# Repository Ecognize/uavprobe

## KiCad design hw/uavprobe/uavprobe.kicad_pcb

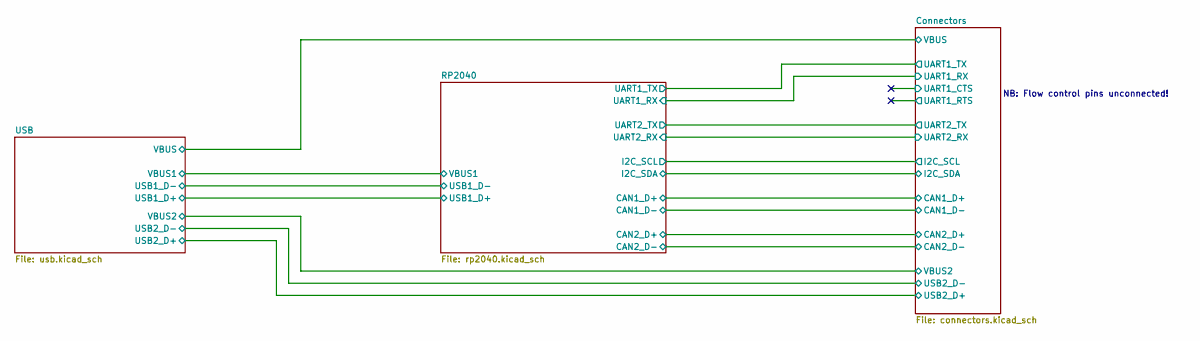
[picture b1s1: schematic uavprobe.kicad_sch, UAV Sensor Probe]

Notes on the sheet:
NB: Flow control pins unconnected!

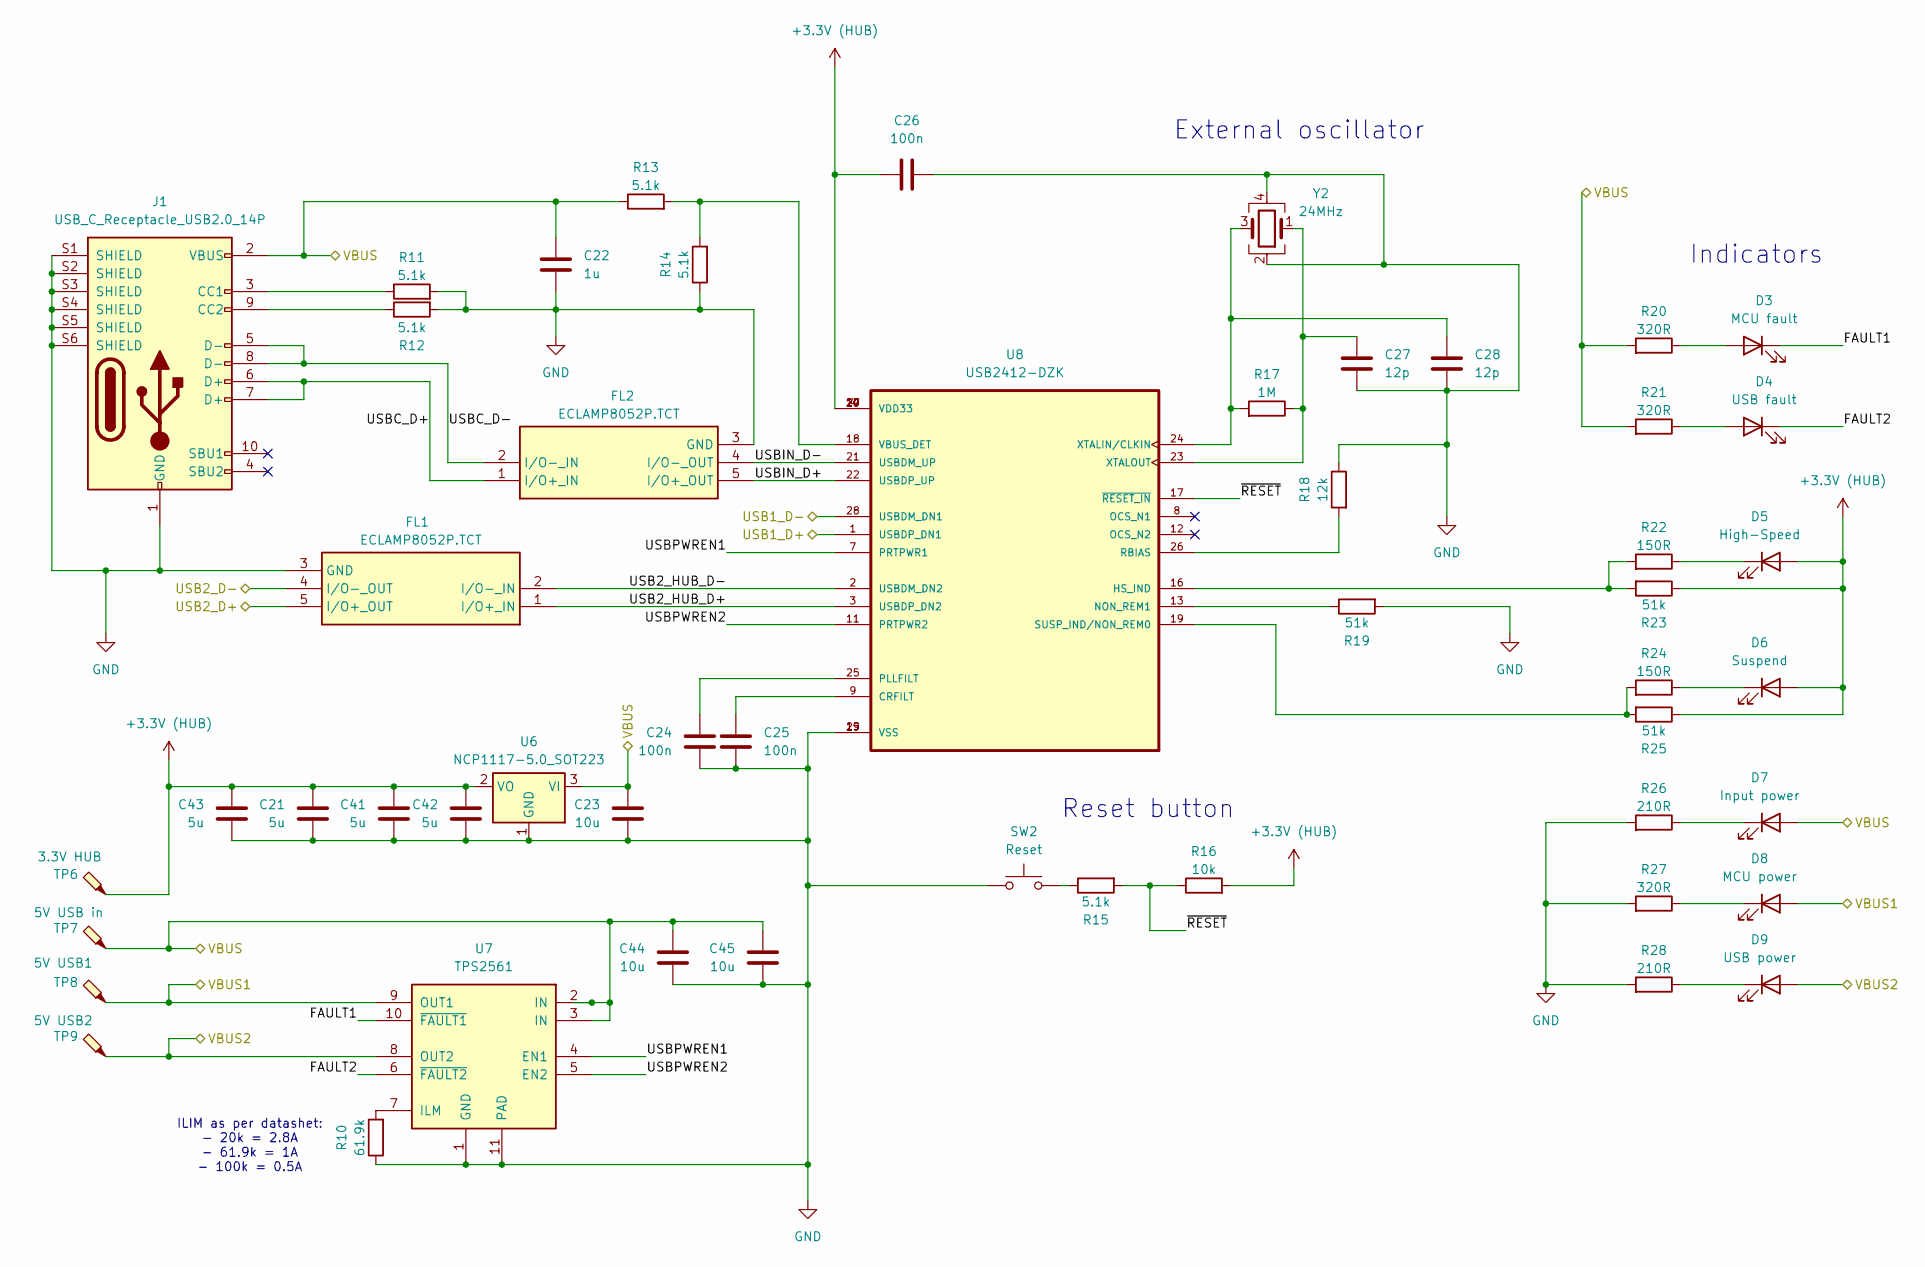
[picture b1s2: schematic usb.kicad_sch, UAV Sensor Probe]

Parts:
C21, C41, C42, C43: 5u; C_0402_1005Metric
C22: 1u; C_0402_1005Metric
C23, C44, C45: 10u; C_0402_1005Metric
C24, C25, C26: 100n; C_0402_1005Metric
C27, C28: 12p; C_0402_1005Metric
D3: MCU fault; LED_0402_1005Metric; MPN QBLP595-R
D4: USB fault; LED_0402_1005Metric; MPN QBLP595-R
D5: High-Speed; LED_0402_1005Metric; MPN QBLP595-O
D6: Suspend; LED_0402_1005Metric; MPN QBLP595-Y
D7: Input power; LED_0402_1005Metric; MPN QBLP595-IG
D8: MCU power; LED_0402_1005Metric; MPN QBLP595-AG
D9: USB power; LED_0402_1005Metric; MPN QBLP595-IB
FL1, FL2: ECLAMP8052P.TCT; ECLAMP8052PTCT; MPN ECLAMP8052P.TCT; Mouser Part Number 947-ECLAMP8052P.TCT
J1: USB_C_Receptacle_USB2.0_14P; JAE_DX07S016JA1R1500; MPN DX07S016JA1R1500
R10: 61.9k; R_0402_1005Metric
R11, R12, R13, R14, R15: 5.1k; R_0402_1005Metric
R16: 10k; R_0402_1005Metric
R17: 1M; R_0402_1005Metric
R18: 12k; R_0402_1005Metric
R19, R23, R25: 51k; R_0402_1005Metric
R20, R21, R27: 320R; R_0402_1005Metric
R22, R24: 150R; R_0402_1005Metric
R26, R28: 210R; R_0402_1005Metric
SW2: Reset; SW_SPST_B3U-1000P; MPN B3U-1000PM
TP6: 3.3V HUB; TestPoint_Pad_D1.5mm
TP7: 5V USB in; TestPoint_Pad_D1.5mm
TP8: 5V USB1; TestPoint_Pad_D1.5mm
TP9: 5V USB2; TestPoint_Pad_D1.5mm
U6: NCP1117-5.0_SOT223; SOT-223-3_TabPin2; MPN NCP1117ST33T3G
U7: TPS2561; VSON-10-1EP_3x3mm_P0.5mm_EP1.65x2.4mm_ThermalVias; MPN TPS2561DRCT
U8: USB2412-DZK; QFN50P500X500X100-29N; MPN USB2412-DZK; DIGI-KEY_PART_NUMBER 638-1114-ND
Y2: 24MHz; Crystal_SMD_Abracon_ABM3B-4Pin_5.0x3.2mm; MPN ABM3B-24.000MHZ-10-1-U-T

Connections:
+3.3V (HUB): C21.1, C26.1, C41.1, C42.1, C43.1, D5.2 (A), D6.2 (A), R16.2, R23.1, R25.1, TP6.1, U6.2 (VO), U8.4 (VDD33), U8.10 (VDD33), U8.14 (VDD33), U8.20 (VDD33), U8.27 (VDD33)
/Connectors/USB2_D+: FL1.5 (I/O+_OUT); also elsewhere on the board
/Connectors/USB2_D-: FL1.4 (I/O-_OUT); also elsewhere on the board
/Connectors/VBUS: C22.1, C23.1, C44.1, C45.1, D7.2 (A), J1.2 (VBUS), J1.11 (VBUS), R13.1, R20.2, R21.2, TP7.1, U6.3 (VI), U7.2 (IN), U7.3 (IN); also elsewhere on the board
/Connectors/VBUS2: D9.2 (A), TP9.1, U7.8 (OUT2); also elsewhere on the board
/RP2040/USB1_D+: U8.1 (USBDP_DN1); also elsewhere on the board
/RP2040/USB1_D-: U8.28 (USBDM_DN1); also elsewhere on the board
/RP2040/VBUS1: D8.2 (A), TP8.1, U7.9 (OUT1); also elsewhere on the board
/USB/FAULT1: D3.1 (K), U7.10 (~FAULT1)
/USB/FAULT2: D4.1 (K), U7.6 (~FAULT2)
/USB/USB2_HUB_D+: FL1.1 (I/O+_IN), U8.3 (USBDP_DN2)
/USB/USB2_HUB_D-: FL1.2 (I/O-_IN), U8.2 (USBDM_DN2)
/USB/USBC_D+: FL2.1 (I/O+_IN), J1.6 (D+), J1.7 (D+)
/USB/USBC_D-: FL2.2 (I/O-_IN), J1.5 (D-), J1.8 (D-)
/USB/USBIN_D+: FL2.5 (I/O+_OUT), U8.22 (USBDP_UP)
/USB/USBIN_D-: FL2.4 (I/O-_OUT), U8.21 (USBDM_UP)
/USB/USBPWREN1: U7.4 (EN1), U8.7 (PRTPWR1)
/USB/USBPWREN2: U7.5 (EN2), U8.11 (PRTPWR2)
/USB/~RESET: R15.2, R16.1, U8.17 (~RESET_IN)
GND: C21.2, C22.2, C23.2, C24.2, C25.2, C26.2, C27.2, C28.2, C41.2, C42.2, C43.2, C44.2, C45.2, FL1.3 (GND), FL2.3 (GND), J1.1 (GND), J1.12 (GND), J1.S1 (SHIELD), J1.S2 (SHIELD), J1.S3 (SHIELD), J1.S4 (SHIELD), J1.S5 (SHIELD), J1.S6 (SHIELD), R10.1, R11.2, R12.2, R14.1, R18.1, R19.2, R26.2, R27.2, R28.2, SW2.1, U6.1 (GND), U7.1 (GND), U7.11 (PAD), U8.15 (VSS), U8.29 (VSS), Y2.2, Y2.4; also elsewhere on the board
unnamed: D3.2 (A), R20.1
unnamed: D4.2 (A), R21.1
unnamed: D5.1 (K), R22.1
unnamed: D6.1 (K), R24.1
unnamed: D7.1 (K), R26.1
unnamed: D8.1 (K), R27.1
unnamed: D9.1 (K), R28.1
unnamed: J1.3 (CC1), R11.1
unnamed: J1.9 (CC2), R12.1
unnamed: R15.1, SW2.2
unnamed: R10.2, U7.7 (ILM)
unnamed: C25.1, U8.9 (CRFILT)
unnamed: R22.2, R23.2, U8.16 (HS_IND)
unnamed: R19.1, U8.13 (NON_REM1)
unnamed: C24.1, U8.25 (PLLFILT)
unnamed: R18.2, U8.26 (RBIAS)
unnamed: R24.2, R25.2, U8.19 (SUSP_IND/NON_REM0)
unnamed: R13.2, R14.2, U8.18 (VBUS_DET)
unnamed: C28.1, R17.2, U8.24 (XTALIN/CLKIN), Y2.3
unnamed: C27.1, R17.1, U8.23 (XTALOUT), Y2.1

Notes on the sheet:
Indicators
ILIM as per datashet: - 20k = 2.8A - 61.9k = 1A - 100k = 0.5A
Reset button
External oscillator

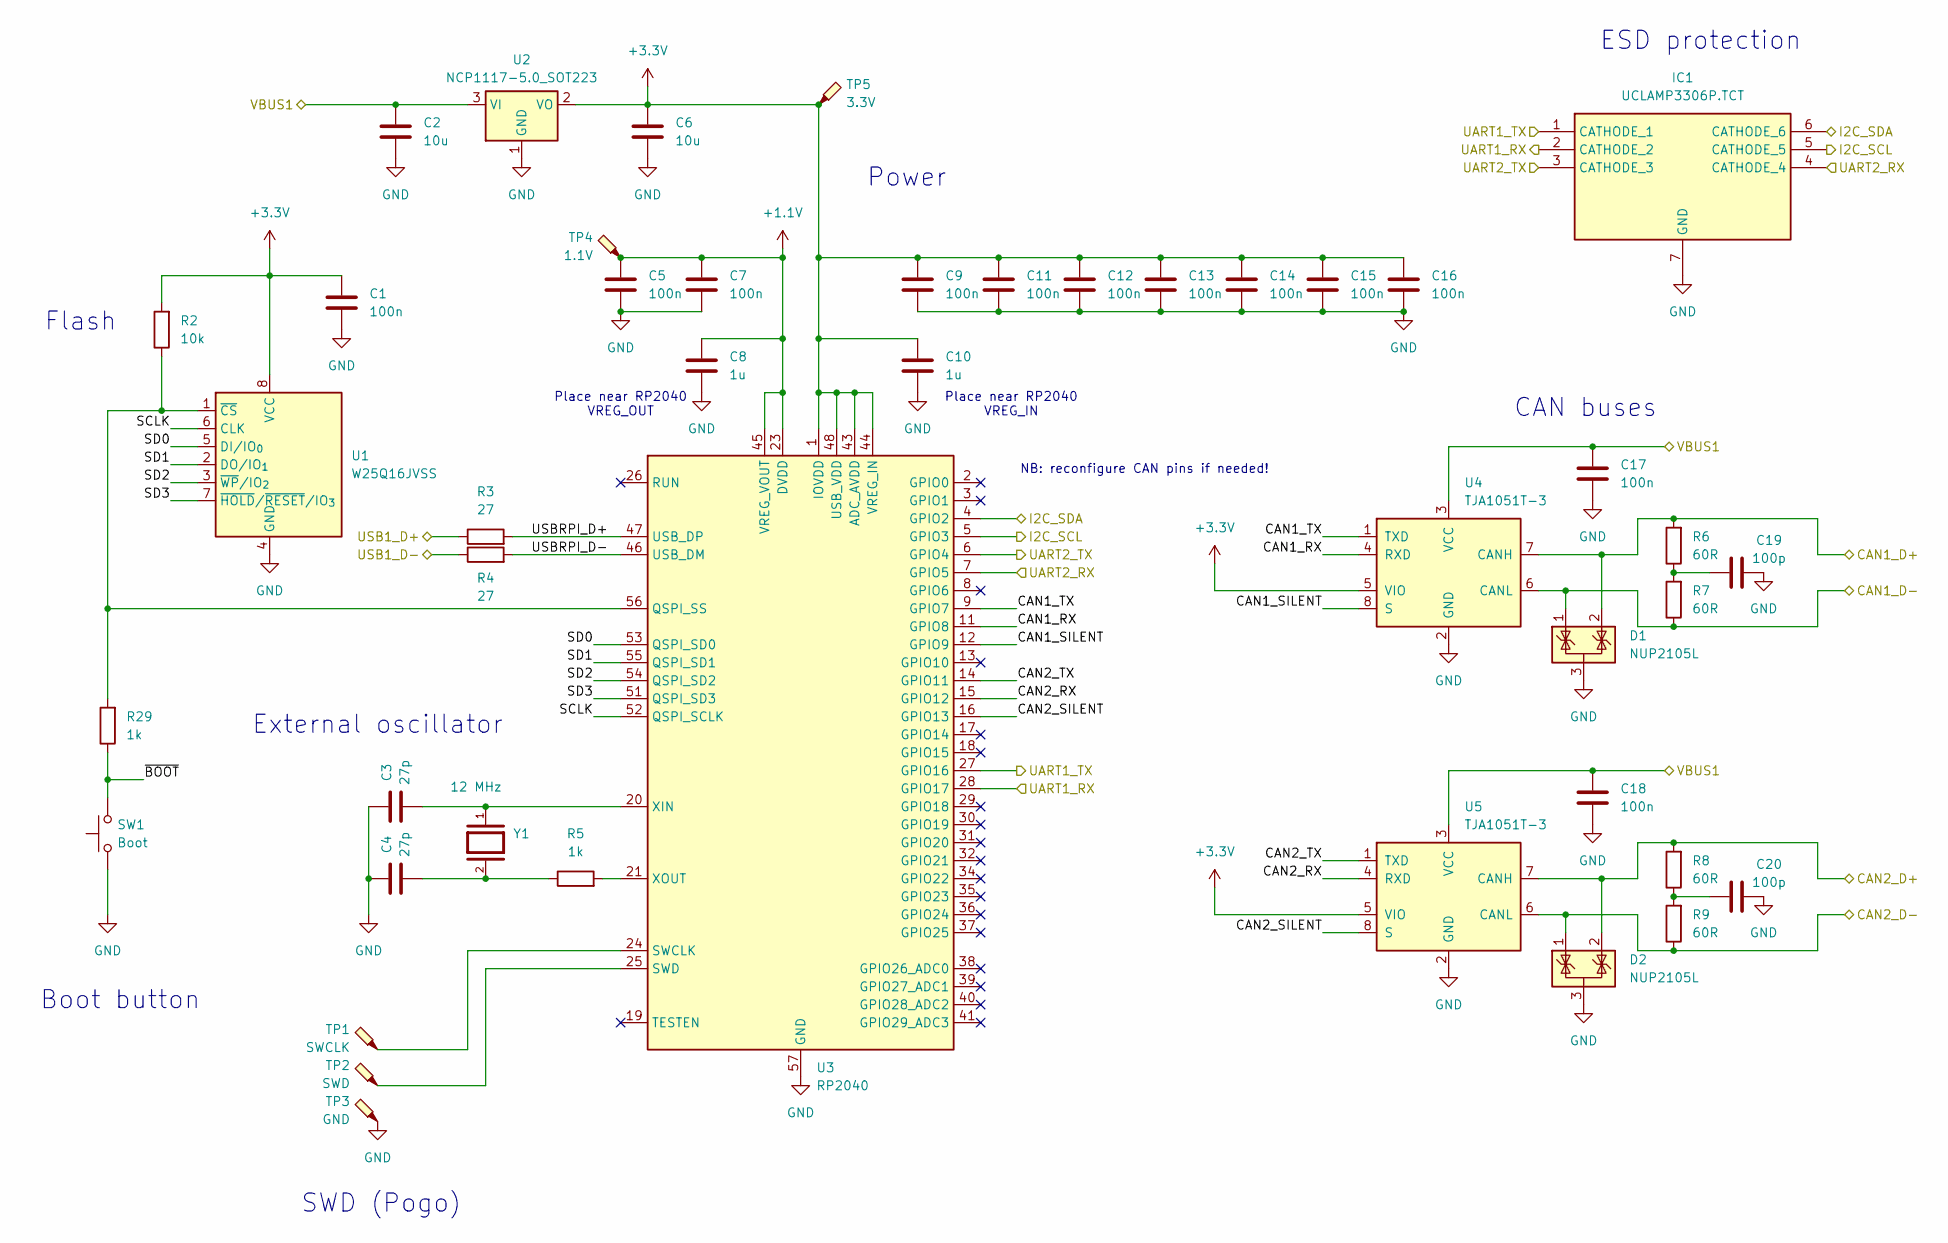
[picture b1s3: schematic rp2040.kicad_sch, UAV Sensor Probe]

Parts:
C1, C5, C7, C9, C11, C12, C13, C14, C15, C16, C17, C18: 100n; C_0402_1005Metric
C2, C6: 10u; C_0402_1005Metric
C3, C4: 27p; C_0402_1005Metric
C8, C10: 1u; C_0402_1005Metric
C19, C20: 100p; C_0402_1005Metric
D1, D2: NUP2105L; SOT-23; MPN NUP2105L
IC1: UCLAMP3306P.TCT; SON50P160X160X65-7N; MPN UCLAMP3306P.TCT; Mouser Part Number 947-UCLAMP3306P.TCT
R2: 10k; R_0402_1005Metric
R3: 27; R_0603_1608Metric
R4: 27; R_0402_1005Metric
R5, R29: 1k; R_0402_1005Metric
R6, R7, R8, R9: 60R; R_0402_1005Metric
SW1: Boot; SW_SPST_B3U-1000P; MPN B3U-1000PM
TP1: SWCLK; TestPoint_Pad_D1.5mm
TP2: SWD; TestPoint_Pad_D1.5mm
TP3: GND; TestPoint_Pad_D1.5mm
TP4: 1.1V; TestPoint_Pad_D1.5mm
TP5: 3.3V; TestPoint_Pad_D1.5mm
U1: W25Q16JVSS; SOIC-8_5.3x5.3mm_P1.27mm; MPN W25Q16JVSSIQ
U2: NCP1117-5.0_SOT223; SOT-223-3_TabPin2; MPN NCP1117ST33T3G
U3: RP2040; QFN-56-1EP_7x7mm_P0.4mm_EP3.2x3.2mm_ThermalVias; MPN SC0914(7)
U4, U5: TJA1051T-3; SOIC-8_3.9x4.9mm_P1.27mm; MPN TJA1051T/3/1J
Y1: 12 MHz; XTAL_ABLS-12.000MHZ-B4-T; PARTREV 02.16.2021

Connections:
+1.1V: C5.1, C7.1, C8.1, TP4.1, U3.23 (DVDD), U3.45 (VREG_VOUT), U3.50 (DVDD)
+3.3V: C1.1, C6.1, C9.1, C10.1, C11.1, C12.1, C13.1, C14.1, C15.1, C16.1, R2.2, TP5.1, U1.8 (VCC), U2.2 (VO), U3.1 (IOVDD), U3.10 (IOVDD), U3.22 (IOVDD), U3.33 (IOVDD), U3.42 (IOVDD), U3.43 (ADC_AVDD), U3.44 (VREG_IN), U3.48 (USB_VDD), U3.49 (IOVDD), U4.5 (VIO), U5.5 (VIO)
/Connectors/CAN1_D+: D1.2 (K), R6.2, U4.7 (CANH); also elsewhere on the board
/Connectors/CAN1_D-: D1.1 (K), R7.1, U4.6 (CANL); also elsewhere on the board
/Connectors/CAN2_D+: D2.2 (K), R8.2, U5.7 (CANH); also elsewhere on the board
/Connectors/CAN2_D-: D2.1 (K), R9.1, U5.6 (CANL); also elsewhere on the board
/Connectors/I2C_SCL: IC1.5 (CATHODE_5), U3.5 (GPIO3); also elsewhere on the board
/Connectors/I2C_SDA: IC1.6 (CATHODE_6), U3.4 (GPIO2); also elsewhere on the board
/Connectors/UART1_RX: IC1.2 (CATHODE_2), U3.28 (GPIO17); also elsewhere on the board
/Connectors/UART1_TX: IC1.1 (CATHODE_1), U3.27 (GPIO16); also elsewhere on the board
/Connectors/UART2_RX: IC1.4 (CATHODE_4), U3.7 (GPIO5); also elsewhere on the board
/Connectors/UART2_TX: IC1.3 (CATHODE_3), U3.6 (GPIO4); also elsewhere on the board
/RP2040/CAN1_RX: U3.11 (GPIO8), U4.4 (RXD)
/RP2040/CAN1_SILENT: U3.12 (GPIO9), U4.8 (S)
/RP2040/CAN1_TX: U3.9 (GPIO7), U4.1 (TXD)
/RP2040/CAN2_RX: U3.15 (GPIO12), U5.4 (RXD)
/RP2040/CAN2_SILENT: U3.16 (GPIO13), U5.8 (S)
/RP2040/CAN2_TX: U3.14 (GPIO11), U5.1 (TXD)
/RP2040/SCLK: U1.6 (CLK), U3.52 (QSPI_SCLK)
/RP2040/SD0: U1.5 (DI/IO_{0}), U3.53 (QSPI_SD0)
/RP2040/SD1: U1.2 (DO/IO_{1}), U3.55 (QSPI_SD1)
/RP2040/SD2: U1.3 (~WP/IO_{2}), U3.54 (QSPI_SD2)
/RP2040/SD3: U1.7 (~HOLD/~RESET/IO_{3}), U3.51 (QSPI_SD3)
/RP2040/USB1_D+: R3.1; also elsewhere on the board
/RP2040/USB1_D-: R4.1; also elsewhere on the board
/RP2040/USBRPI_D+: R3.2, U3.47 (USB_DP)
/RP2040/USBRPI_D-: R4.2, U3.46 (USB_DM)
/RP2040/VBUS1: C2.1, C17.1, C18.1, U2.3 (VI), U4.3 (VCC), U5.3 (VCC); also elsewhere on the board
/RP2040/~BOOT: R29.1, SW1.2
GND: C1.2, C2.2, C3.1, C4.1, C5.2, C6.2, C7.2, C8.2, C9.2, C10.2, C11.2, C12.2, C13.2, C14.2, C15.2, C16.2, C17.2, C18.2, C19.1, C20.1, D1.3 (A), D2.3 (A), IC1.7 (GND), SW1.1, TP3.1, U1.4 (GND), U2.1 (GND), U3.57 (GND), U4.2 (GND), U5.2 (GND); also elsewhere on the board
unnamed: C4.2, R5.1, Y1.2
unnamed: C19.2, R6.1, R7.2
unnamed: C20.2, R8.1, R9.2
unnamed: R2.1, R29.2, U1.1 (~CS), U3.56 (QSPI_SS)
unnamed: TP1.1, U3.24 (SWCLK)
unnamed: TP2.1, U3.25 (SWD)
unnamed: C3.2, U3.20 (XIN), Y1.1
unnamed: R5.2, U3.21 (XOUT)

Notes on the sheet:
Power
Place near RP2040 VREG_OUT
ESD protection
CAN buses
Flash
Place near RP2040 VREG_IN
NB: reconfigure CAN pins if needed!
Boot button
SWD (Pogo)
External oscillator

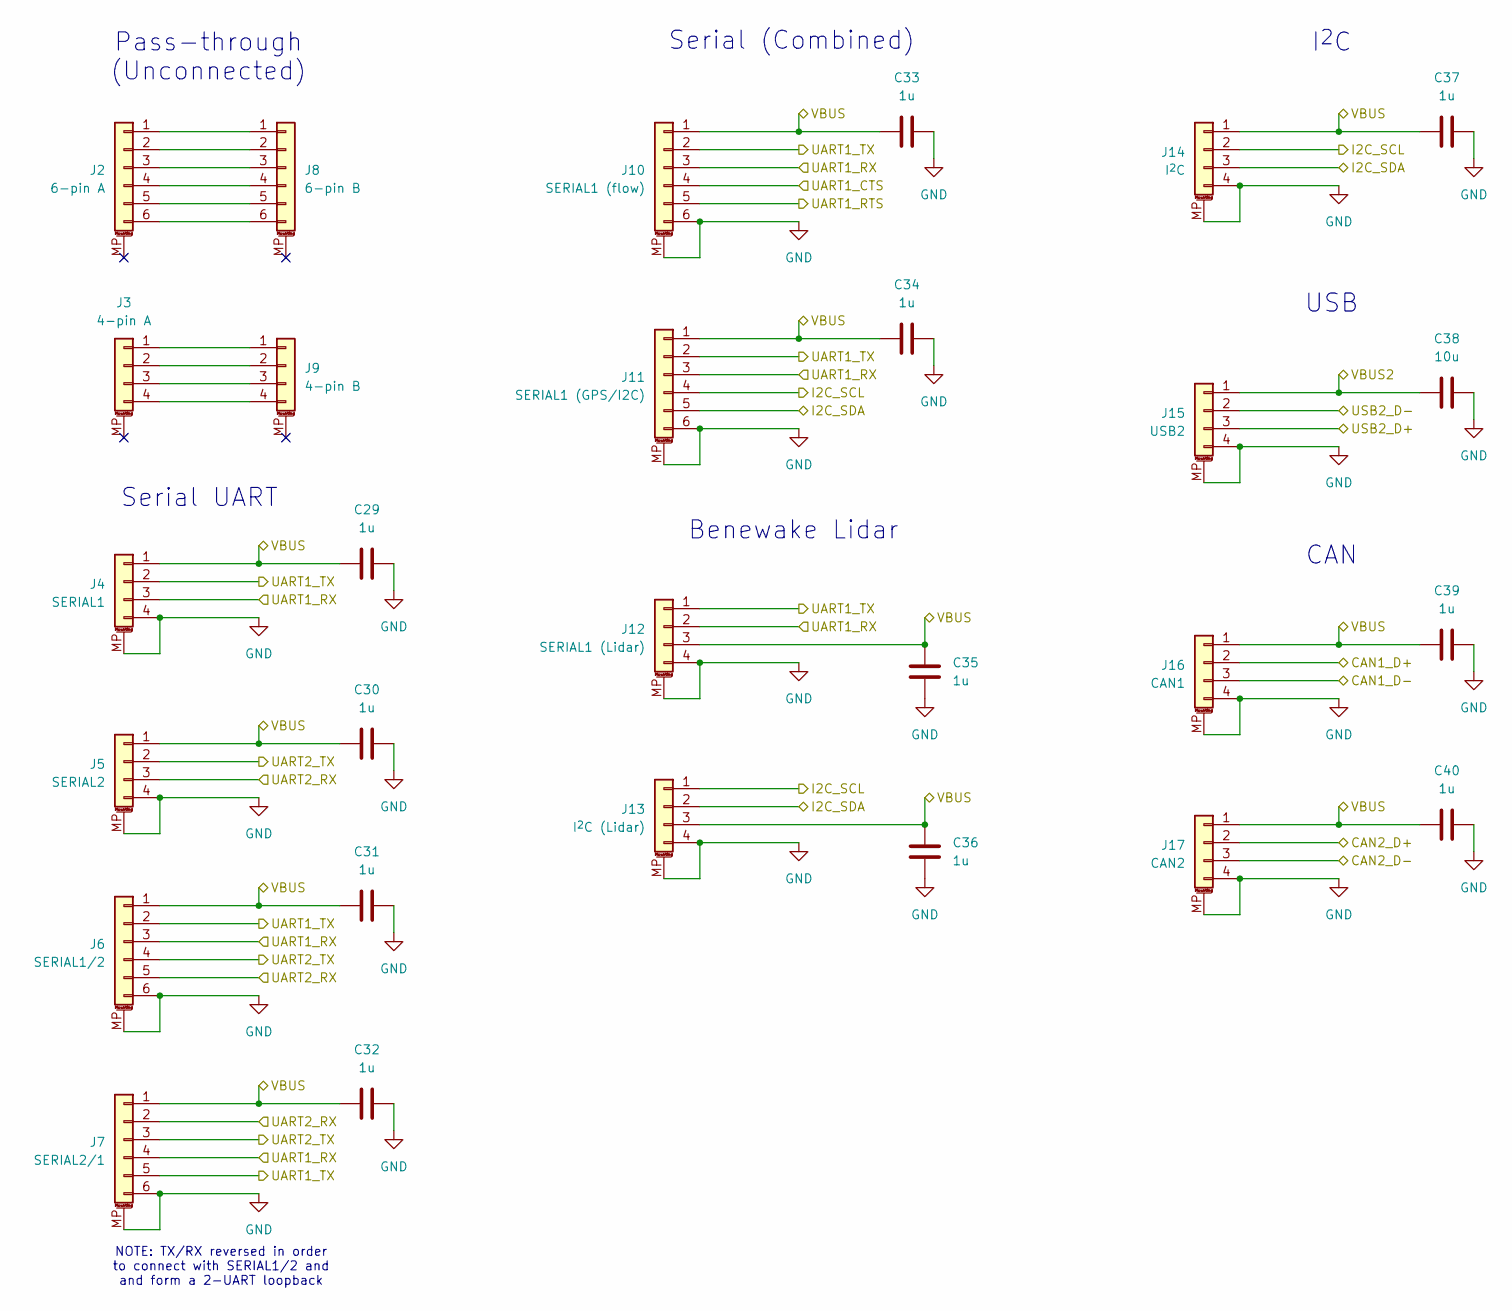
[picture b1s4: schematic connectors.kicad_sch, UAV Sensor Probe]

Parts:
C29, C30, C31, C32, C33, C34, C35, C36, C37, C39, C40: 1u; C_0402_1005Metric
C38: 10u; C_0402_1005Metric
J2: 6-pin A; JST_GH_BM06B-GHS-TBT_1x06-1MP_P1.25mm_Vertical; MPN BM06B-GHS-TBT
J3: 4-pin A; JST_GH_BM04B-GHS-TBT_1x04-1MP_P1.25mm_Vertical; MPN BM04B-GHS-TBT
J4: SERIAL1; JST_GH_BM04B-GHS-TBT_1x04-1MP_P1.25mm_Vertical; MPN BM04B-GHS-TBT
J5: SERIAL2; JST_GH_BM04B-GHS-TBT_1x04-1MP_P1.25mm_Vertical; MPN BM04B-GHS-TBT
J6: SERIAL1/2; JST_GH_BM06B-GHS-TBT_1x06-1MP_P1.25mm_Vertical; MPN BM06B-GHS-TBT
J7: SERIAL2/1; JST_GH_BM06B-GHS-TBT_1x06-1MP_P1.25mm_Vertical; MPN BM06B-GHS-TBT
J8: 6-pin B; JST_GH_BM06B-GHS-TBT_1x06-1MP_P1.25mm_Vertical; MPN BM06B-GHS-TBT
J9: 4-pin B; JST_GH_BM04B-GHS-TBT_1x04-1MP_P1.25mm_Vertical; MPN BM04B-GHS-TBT
J10: SERIAL1 (flow); JST_GH_BM06B-GHS-TBT_1x06-1MP_P1.25mm_Vertical; MPN BM06B-GHS-TBT
J11: SERIAL1 (GPS/I2C); JST_GH_BM06B-GHS-TBT_1x06-1MP_P1.25mm_Vertical; MPN BM06B-GHS-TBT
J12: SERIAL1 (Lidar); JST_GH_BM04B-GHS-TBT_1x04-1MP_P1.25mm_Vertical; MPN BM04B-GHS-TBT
J13: I^{2}C (Lidar); JST_GH_BM04B-GHS-TBT_1x04-1MP_P1.25mm_Vertical; MPN BM04B-GHS-TBT
J14: I^{2}C; JST_GH_BM04B-GHS-TBT_1x04-1MP_P1.25mm_Vertical; MPN BM04B-GHS-TBT
J15: USB2; JST_GH_BM04B-GHS-TBT_1x04-1MP_P1.25mm_Vertical; MPN BM04B-GHS-TBT
J16: CAN1; JST_GH_BM04B-GHS-TBT_1x04-1MP_P1.25mm_Vertical; MPN BM04B-GHS-TBT
J17: CAN2; JST_GH_BM04B-GHS-TBT_1x04-1MP_P1.25mm_Vertical; MPN BM04B-GHS-TBT

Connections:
/Connectors/CAN1_D+: J16.2; also elsewhere on the board
/Connectors/CAN1_D-: J16.3; also elsewhere on the board
/Connectors/CAN2_D+: J17.2; also elsewhere on the board
/Connectors/CAN2_D-: J17.3; also elsewhere on the board
/Connectors/I2C_SCL: J11.4, J13.1, J14.2; also elsewhere on the board
/Connectors/I2C_SDA: J11.5, J13.2, J14.3; also elsewhere on the board
/Connectors/UART1_CTS: J10.4
/Connectors/UART1_RTS: J10.5
/Connectors/UART1_RX: J4.3, J6.3, J7.4, J10.3, J11.3, J12.2; also elsewhere on the board
/Connectors/UART1_TX: J4.2, J6.2, J7.5, J10.2, J11.2, J12.1; also elsewhere on the board
/Connectors/UART2_RX: J5.3, J6.5, J7.2; also elsewhere on the board
/Connectors/UART2_TX: J5.2, J6.4, J7.3; also elsewhere on the board
/Connectors/USB2_D+: J15.3; also elsewhere on the board
/Connectors/USB2_D-: J15.2; also elsewhere on the board
/Connectors/VBUS: C29.1, C30.1, C31.1, C32.1, C33.1, C34.1, C35.2, C36.2, C37.1, C39.1, C40.1, J4.1, J5.1, J6.1, J7.1, J10.1, J11.1, J12.3, J13.3, J14.1, J16.1, J17.1; also elsewhere on the board
/Connectors/VBUS2: C38.1, J15.1; also elsewhere on the board
GND: C29.2, C30.2, C31.2, C32.2, C33.2, C34.2, C35.1, C36.1, C37.2, C38.2, C39.2, C40.2, J4.4, J4.MP (MountPin), J5.4, J5.MP (MountPin), J6.6, J6.MP (MountPin), J7.6, J7.MP (MountPin), J10.6, J10.MP (MountPin), J11.6, J11.MP (MountPin), J12.4, J12.MP (MountPin), J13.4, J13.MP (MountPin), J14.4, J14.MP (MountPin), J15.4, J15.MP (MountPin), J16.4, J16.MP (MountPin), J17.4, J17.MP (MountPin); also elsewhere on the board
unnamed: J2.1, J8.1
unnamed: J2.2, J8.2
unnamed: J2.3, J8.3
unnamed: J2.4, J8.4
unnamed: J2.5, J8.5
unnamed: J2.6, J8.6
unnamed: J3.1, J9.1
unnamed: J3.2, J9.2
unnamed: J3.3, J9.3
unnamed: J3.4, J9.4

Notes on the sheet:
USB
Serial (Combined)
Benewake Lidar
Pass-through (Unconnected)
Serial UART
I^{2}C
NOTE: TX/RX reversed in order to connect with SERIAL1/2 and and form a 2-UART loopback
CAN

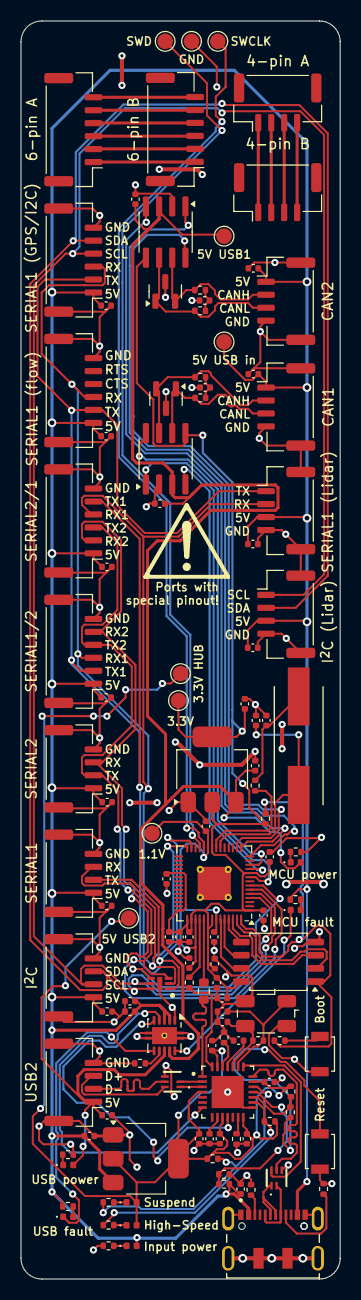
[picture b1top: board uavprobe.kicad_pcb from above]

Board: 2 copper layers, 30.8 x 121.4 mm, 123 parts (0 on the bottom side), 84 nets.

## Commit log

2025-08-24 AISLER from template
    2 layer HASL
2025-08-26 RP2040 sheet
2025-08-26 Connectors sheet and CAN/ESD
2025-08-26 CAN ESD protection
2025-08-26 USB sheet
2025-08-26 Cleanup and root sheet
2025-08-26 Power test points
2025-08-26 ERC pass
    Footprint and symbol copy editing warnings left
2025-08-27 Footprint/MPN assignment pass
2025-08-27 Components import and model setup
2025-08-28 Design rules and net classes
2025-08-29 Training layout
    Lessons were learned, let's restart.
2025-08-30 Layout revision 1
    Pre-DRC
2025-08-30 AISLER-friendly BOM fields
2025-08-31 3D models fix for imported components
2025-09-01 Official AISLER HASL 2-layer rules
2025-09-05 Layout 2
    Honoring the DRC and with a new uSB-C connector
2025-09-05 Edge cleaning
2025-09-06 USB-C connector 3D model
2025-09-06 Back silkscreen
2025-09-06 USB-C connector change
2025-10-03 LEDs reconfigured for 10 mA current
